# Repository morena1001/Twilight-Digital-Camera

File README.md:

# Twilight-Digital-Camera
This digital camera uses the OV2640 camera sensor on the Seeed Studio XIAO ESP32 S3 Sense to take pictures, and DSP to apply a filter to achieve that iconic Twilight movie look.

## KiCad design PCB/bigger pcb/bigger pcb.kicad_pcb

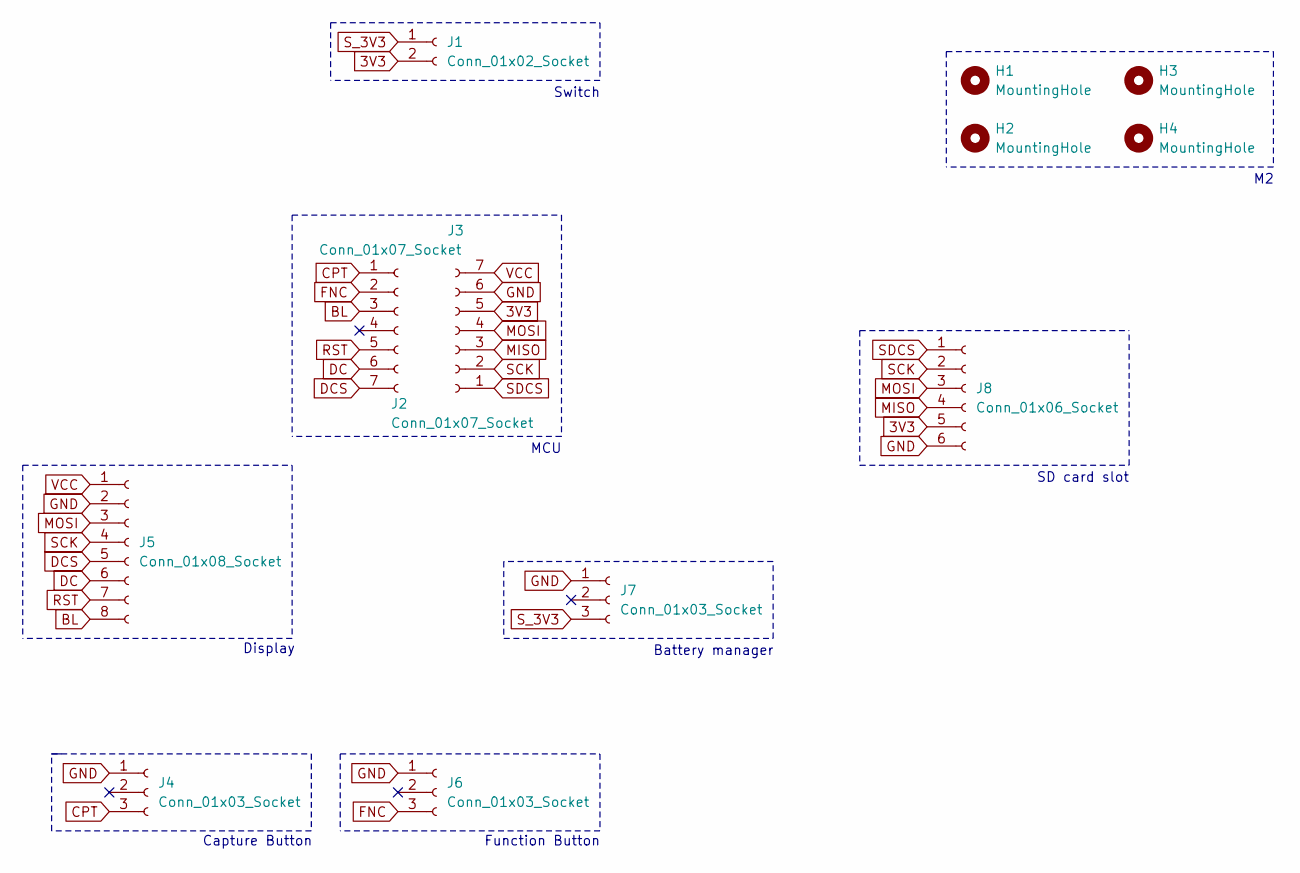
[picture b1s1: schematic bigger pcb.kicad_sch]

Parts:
H1, H2, H3, H4: MountingHole; MountingHole_2.2mm_M2
J1: Conn_01x02_Socket; PinHeader_1x02_P2.54mm_Vertical
J2, J3: Conn_01x07_Socket; PinHeader_1x07_P2.54mm_Vertical
J4, J6, J7: Conn_01x03_Socket; PinHeader_1x03_P2.54mm_Vertical
J5: Conn_01x08_Socket; PinHeader_1x08_P2.54mm_Vertical
J8: Conn_01x06_Socket; PinHeader_1x06_P2.54mm_Vertical

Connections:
3V3: J1.2, J3.5, J8.5
BL: J2.3, J5.8
CPT: J2.1, J4.3
DC: J2.6, J5.6
DCS: J2.7, J5.5
FNC: J2.2, J6.3
GND: J3.6, J4.1, J5.2, J6.1, J7.1, J8.6
MISO: J3.3, J8.4
MOSI: J3.4, J5.3, J8.3
RST: J2.5, J5.7
SCK: J3.2, J5.4, J8.2
SDCS: J3.1, J8.1
S_3V3: J1.1, J7.3
VCC: J3.7, J5.1

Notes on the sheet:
Switch
Capture Button
Display
SD card slot
Battery manager
Function Button
MCU

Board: 2 copper layers, 12 parts (0 on the bottom side), 14 nets, no tracks yet.

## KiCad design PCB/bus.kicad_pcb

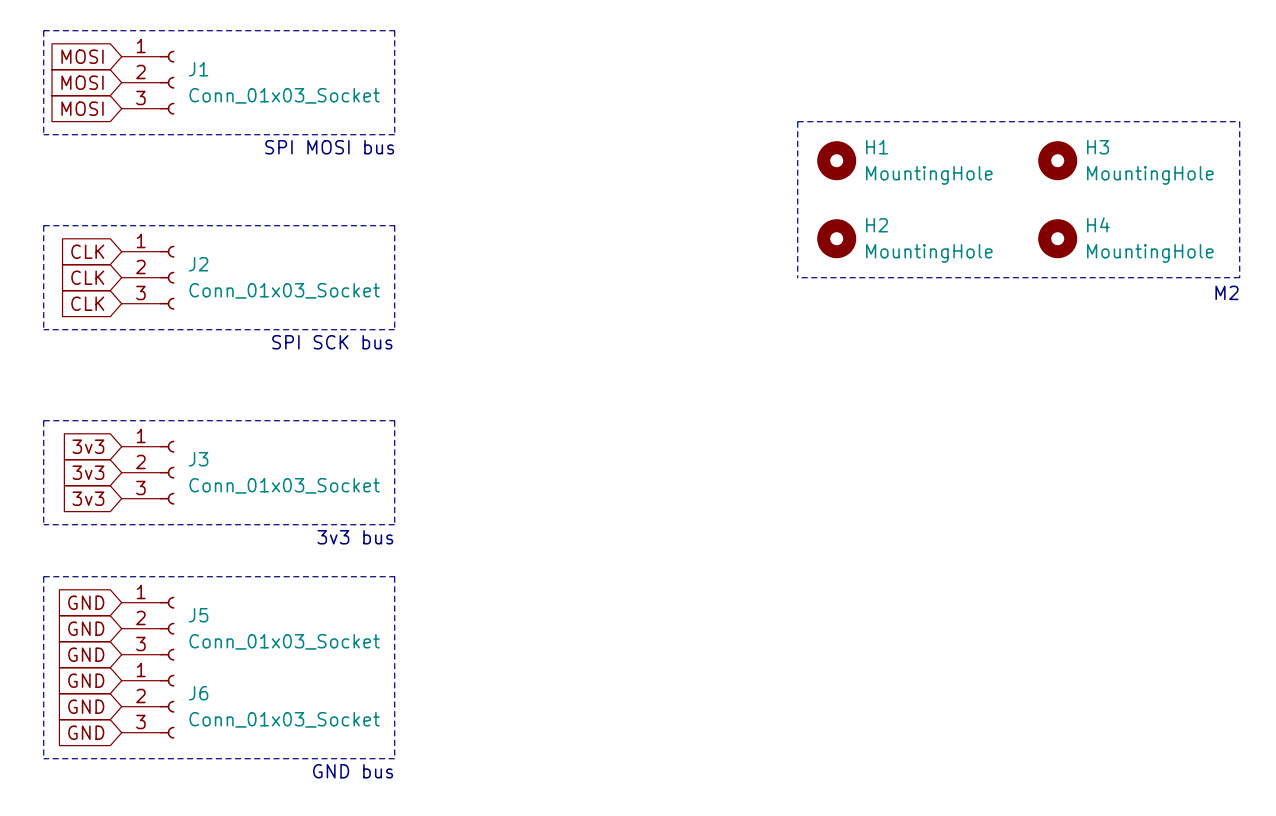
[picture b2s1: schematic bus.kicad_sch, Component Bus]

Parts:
H1, H2, H3, H4: MountingHole; MountingHole_2.2mm_M2
J1, J2, J3, J5, J6: Conn_01x03_Socket; PinHeader_1x03_P2.54mm_Vertical

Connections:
3v3: J3.1, J3.2, J3.3
CLK: J2.1, J2.2, J2.3
GND: J5.1, J5.2, J5.3, J6.1, J6.2, J6.3
MOSI: J1.1, J1.2, J1.3

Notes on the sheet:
SPI SCK bus
GND bus
SPI MOSI bus
3v3 bus

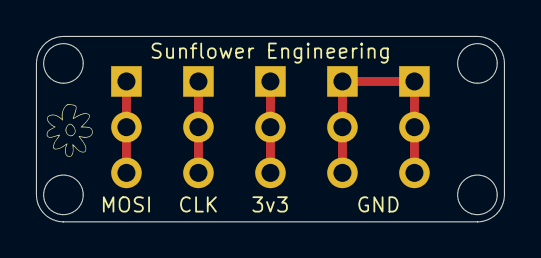
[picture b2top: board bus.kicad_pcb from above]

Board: 2 copper layers, 26.0 x 10.3 mm, 9 parts (0 on the bottom side), 4 nets.
